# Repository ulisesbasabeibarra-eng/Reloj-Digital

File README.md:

# Reloj Digital

## Authors

- [@Ulises Basabe](https://github.com/ulisesbasabeibarra-eng)
- [@Facundo Dominguez](https://github.com/facundodominguez1)
- [@Ramiro Trejo](https://github.com/RamiiTrejo)
- [@Rodrigo Benitez](https://github.com/rodrigobenitez17)
- [@Maximo Paez]()

## DESCRIPCIÓN

Un reloj digital sin utilizar un microcontrolador o web para establecer el tiempo. Utilizando solamente electronica discreta como el lm555, cuyo componente debe de estar en modo astable para general pulsos electronicos que estableceran gracias a los integrados 74LS47 y 74LS90 que los displays de 7 segmentos marquen una hora determinada. Un total de 6 displays para marcar los segundos, minutos y horas.
## Informe

[Video en proteus](https://www.youtube.com/watch?v=-MJHPHdGoc4)

[Reloj Digital](https://docs.google.com/document/d/12YXhhFJf7GPLBze2eZ5sYaiuNMOwRFxj9prBwNTrKLU/edit?pli=1&tab=t.0#heading=h.a97jr9uy2bgi)
. Este enlace lleva a un documento de google en el que se encuentra más informacion sobre este projecto junto con imagenes explicativas y vistas previas.
## Funcionamiento
El funcionamiento de este reloj se basa en el circuito integrado LM555, configurado como oscilador astable, que genera una serie de pulsos eléctricos aproximadamente de 1 Hz por  segundo. Estos pulsos son enviados al 74LS90, que actúa como contador decimal y convierte los pulsos en una salida binaria. Después, esta señal binaria pasa al 74LS47, que la decodifica y la transforma en señales para encender los segmentos correspondientes del display de 7 segmentos, mostrando así los números de forma digital. 

El potenciómetro permite ajustar la frecuencia del LM555, aumentando o disminuyendo la velocidad con que se generan los pulsos que llegan al 74LS90 (Es decir, la velocidad con que se cambian los números en el display).

El LED conectado al circuito también parpadea al ritmo de los pulsos, sirviendo como indicador visual de la frecuencia del contador. En este caso, se ha optado por utilizar una resistencia fija de 3,9 kΩ, de modo que el temporizador genere un pulso cada segundo aproximadamente, obteniendo así una base de tiempo estable para el reloj.

Los botones conectados uno a los displays de los segundos y otro conectado a los minutos. Su funcion es que una vez al ser pulsados, este pulso contara tambien como si fuera un pulso del LM555, es decir, una vez que se pulsa el numero del display pasara al siguiente respectivamente, funcionando como un reloj manual y esta para setiar el reloj a la hora exacta al de la hora actual.

(La alimentacion vendria mediante un cable conectado a un transformador el cual iria conectado a un toma corriente)
## Modelo 3D
En este projecto se utilizo Autodesk, plataforma de software el cual estoy mas acostumbrado a utilizar ademas de ser muy utilizadas a la hora de hacer diseños 3D, gracias a que este ofrece una amplia gama de software como AutoCAD, Fusion 360, Inventor y 3ds Max, utilizados en sectores como la ingeniería, la arquitectura, el entretenimiento y el diseño de productos.

El modelo 3D esta compuesto por dos partes principales: El piso y El cuerpo. 

El piso o la inferior, es un rectangulo compuesto por cuatro agujeros, uno en cada esquina, por donde se ingresarian los tornillos los cuales unirian las dos piezas. Además de tener otros cuatro agujeros más con un desnivel para ubicar la placa y mantenerla en el lugar y dejando un muy pequeño espacio entre los dos para las patas o sobresalientes de los componentes de la misma.

El Cuepo tambien consta con los mismos huecos para tener mas rigidez en la uniones de estas tres partes (placa, piso, cuerpo).Tambien consta con un agujero en un costado para permitir la salida del cable de alimentación.

Además tiene 6 agujeros rectangulares para permitir la vista de los displays de 7 segmento, con una pequeña separacion entre cada uno y otra entre cada grupo de dos, para formar los segundos, minutos y horas, cuyos grupos abajo les sigue sus respectivo unidad marcada como un corte en el cuerpo. Tambien, más abajo tiene dos agueros donde irian ubicados los botones. Los displays y los botones deberan ir adheridos con silicona para que mantengan su lugar.

En la carpeta carcasa, se encontran los archivos de estas pieza 3D en diferentes tipos de archivos desde .stl, donde se podran mandar a imprimir directamente, .fusion, asta .step. 
## Desmontaje de la carcasa

 se observa como se vería el diseño de la plaqueta en 3D para poder dimensionar los componentes y facilitar la comprension de las conexiones

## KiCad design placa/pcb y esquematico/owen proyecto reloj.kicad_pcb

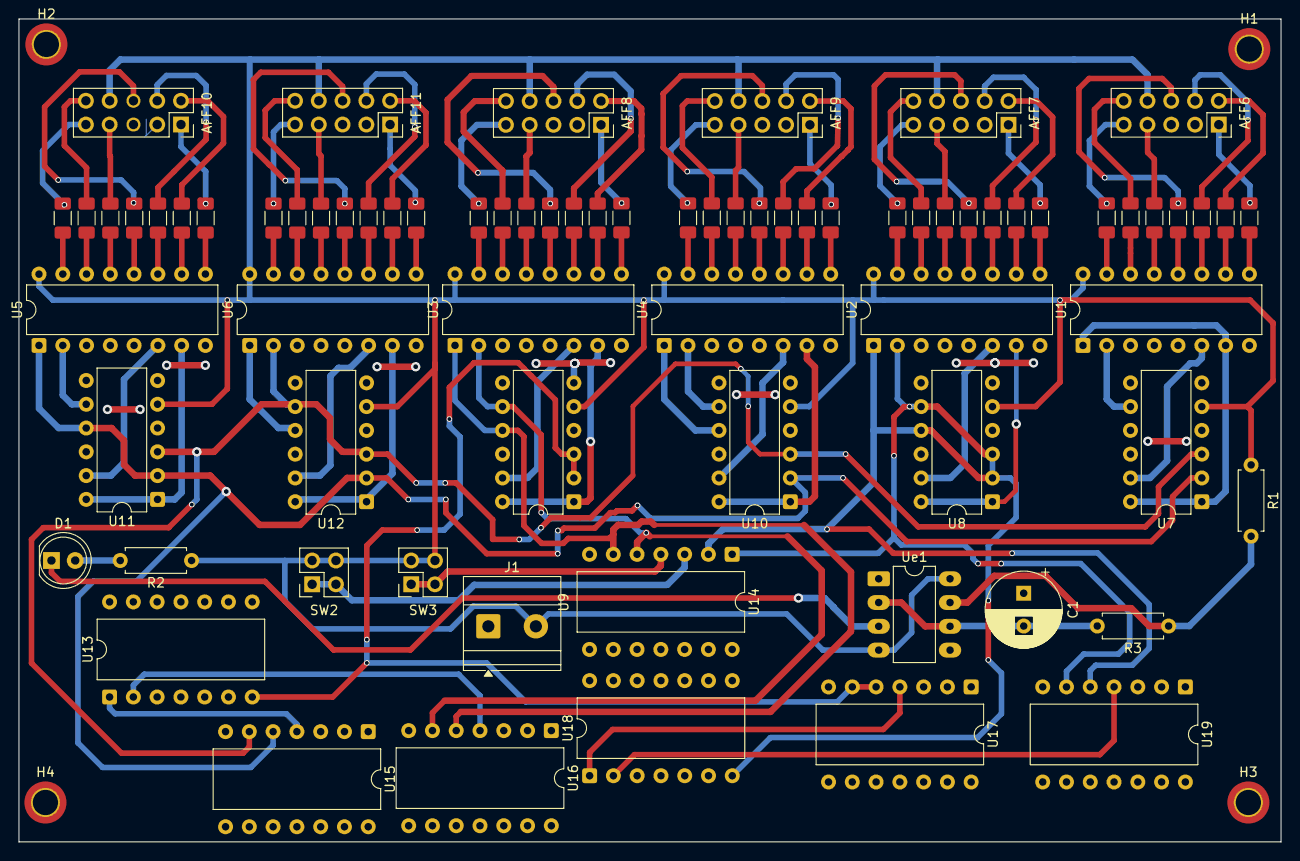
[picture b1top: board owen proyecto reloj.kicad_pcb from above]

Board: 2 copper layers, 134.8 x 87.9 mm, 80 parts (0 on the bottom side), 121 nets.

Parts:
AFF6, AFF7, AFF8, AFF9, AFF10, AFF11: LTS-6960HR; PinSocket_2x05_P2.54mm_Vertical
C1: C; CP_Radial_D8.0mm_P3.50mm
D1: LED; LED_D5.0mm
H1, H2, H3, H4: Mounting_Hole; MountingHole_2.7mm_M2.5_ISO14580_Pad_TopOnly
J1: Screw_Terminal_01x02; TerminalBlock_Phoenix_MKDS-1,5-2-5.08_1x02_P5.08mm_Horizont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
R1: 4.7K; R_Axial_DIN0207_L6.3mm_D2.5mm_P7.62mm_Horizontal
R2: 330; R_Axial_DIN0207_L6.3mm_D2.5mm_P7.62mm_Horizontal
R3: 3.9k; R_Axial_DIN0207_L6.3mm_D2.5mm_P7.62mm_Horizontal
R10, R11, R12, R13, R14, R15, R16, R17, R18, R19, R20, R21, R22, R23, R24, R25, R26, R27, R28, R29, R30, R31, R32, R33, R34, R35, R36, R37, R38, R39, R40, R41, R42, R43, R44, R45, R46, R47, R48, R49, R50, R51: 330; R_1206_3216Metric_Pad1.30x1.75mm_HandSolder
SW2, SW3: SW_MEC_5G; PinSocket_2x02_P2.54mm_Vertical
U1, U2, U3, U4, U5, U6: 74LS47; DIP-16_W7.62mm
U7, U8, U9, U10, U11, U12: 74LS90; DIP-12_W7.62mm
U13, U18: 74AUC2G32; DIP-14_W10.16mm
U14, U15, U16, U17, U19: 4081; DIP-14_W10.16mm
Ue1: LM555xM; DIP-8_W7.62mm_LongPads

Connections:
A1: AFF10.7 (a), R38.1
A2: AFF11.7 (a), R31.1
A3: AFF8.7 (a), R24.1
A4: AFF9.7 (a), R17.1
A5: AFF7.7 (a), R10.1
A6: AFF6.7 (a), R45.1
B1: AFF10.6 (b), R39.1
B2: AFF11.6 (b), R32.1
B3: AFF8.6 (b), R25.1
B4: AFF9.6 (b), R18.1
B5: AFF7.6 (b), R11.1
B6: AFF6.6 (b), R46.1
C1: AFF10.4 (c), R40.1
C2: AFF11.4 (c), R33.1
C3: AFF8.4 (c), R26.1
C4: AFF9.4 (c), R19.1
C5: AFF7.4 (c), R12.1
C6: AFF6.4 (c), R47.1
D1: AFF10.2 (d), R41.1
D2: AFF11.2 (d), R34.1
D3: AFF8.2 (d), R27.1
D4: AFF9.2 (d), R20.1
D5: AFF7.2 (d), R13.1
D6: AFF6.2 (d), R48.1
E1: AFF10.1 (e), R42.1
E2: AFF11.1 (e), R35.1
E3: AFF8.1 (e), R28.1
E4: AFF9.1 (e), R21.1
E5: AFF7.1 (e), R14.1
E6: AFF6.1 (e), R49.1
F1: AFF10.9 (f), R43.1
F2: AFF11.9 (f), R36.1
F3: AFF8.9 (f), R29.1
F4: AFF9.9 (f), R22.1
F5: AFF7.9 (f), R15.1
F6: AFF6.9 (f), R50.1
G1: AFF10.10 (g), R44.1
G2: AFF11.10 (g), R37.1
G3: AFF8.10 (g), R30.1
G4: AFF9.10 (g), R23.1
G5: AFF7.10 (g), R16.1
G6: AFF6.10 (g), R51.1
GND: C1.1, J1.1, U1.8 (GND), U2.8 (GND), U3.8 (GND), U4.8 (GND), U5.8 (GND), U6.8 (GND), U7.6 (R9(1)), U7.7 (R9(2)), U7.10 (GND), U8.6 (R9(1)), U8.7 (R9(2)), U8.10 (GND), U9.6 (R9(1)), U9.7 (R9(2)), U9.10 (GND), U10.6 (R9(1)), U10.7 (R9(2)), U10.10 (GND), U11.6 (R9(1)), U11.7 (R9(2)), U11.10 (GND), U12.6 (R9(1)), U12.7 (R9(2)), U12.10 (GND), Ue1.1 (GND)
unnamed: D1.2 (A), R2.2
unnamed: R45.2, U1.13 (a)
unnamed: R46.2, U1.12 (b)
unnamed: R47.2, U1.11 (c)
unnamed: R48.2, U1.10 (d)
unnamed: R49.2, U1.9 (e)
unnamed: R50.2, U1.15 (f)
unnamed: R51.2, U1.14 (g)
unnamed: R10.2, U2.13 (a)
unnamed: R11.2, U2.12 (b)
unnamed: R12.2, U2.11 (c)
unnamed: R13.2, U2.10 (d)
unnamed: R14.2, U2.9 (e)
unnamed: R15.2, U2.15 (f)
unnamed: R16.2, U2.14 (g)
unnamed: R24.2, U3.13 (a)
unnamed: R25.2, U3.12 (b)
unnamed: R26.2, U3.11 (c)
unnamed: R27.2, U3.10 (d)
unnamed: R28.2, U3.9 (e)
unnamed: R29.2, U3.15 (f)
unnamed: R30.2, U3.14 (g)
unnamed: R17.2, U4.13 (a)
unnamed: R18.2, U4.12 (b)
unnamed: R19.2, U4.11 (c)
unnamed: R20.2, U4.10 (d)
unnamed: R21.2, U4.9 (e)
unnamed: R22.2, U4.15 (f)
unnamed: R23.2, U4.14 (g)
unnamed: R38.2, U5.13 (a)
unnamed: R39.2, U5.12 (b)
unnamed: R40.2, U5.11 (c)
unnamed: R41.2, U5.10 (d)
unnamed: R42.2, U5.9 (e)
unnamed: R43.2, U5.15 (f)
unnamed: R44.2, U5.14 (g)
unnamed: R31.2, U6.13 (a)
unnamed: R32.2, U6.12 (b)
unnamed: R33.2, U6.11 (c)
unnamed: R34.2, U6.10 (d)
unnamed: R35.2, U6.9 (e)
unnamed: R36.2, U6.15 (f)
unnamed: R37.2, U6.14 (g)
unnamed: U13.1, U15.4
unnamed: U13.2, U16.4
unnamed: U17.4, U18.1
unnamed: U18.2, U19.4
unnamed: R1.2, R3.1, Ue1.7 (DIS)
Out: D1.1 (K), Ue1.3 (Q)
Q0: U5.7 (A), U11.1 (CP1..3), U11.12 (Q0)
Q1: U5.1 (B), U7.2 (R0(1)), U10.2 (R0(1)), U11.2 (R0(1)), U11.9 (Q1), U12.2 (R0(1)), U15.5
Q3: U5.2 (C), U11.8 (Q2)
Q4: U5.6 (D), U11.11 (Q3)
Q5: U6.7 (A), U12.1 (CP1..3), U12.12 (Q0)
Q6: U6.1 (B), U12.9 (Q1)
Q7: U6.2 (C), U7.3 (R0(2)), U10.3 (R0(2)), U11.3 (R0(2)), U12.3 (R0(2)), U12.8 (Q2), U15.6
Q8: U6.6 (D), U12.11 (Q3)
Q9: U3.7 (A), U9.1 (CP1..3), U9.12 (Q0)
Q10: U3.1 (B), U9.9 (Q1), U14.6, U16.5
Q11: U3.2 (C), U9.8 (Q2), U14.5, U16.6
Q12: U3.6 (D), U9.11 (Q3)
Q13: U4.7 (A), U10.1 (CP1..3), U10.12 (Q0)
Q14: U4.1 (B), U10.9 (Q1)
Q15: U4.2 (C), U10.8 (Q2)
Q16: U4.6 (D), U10.11 (Q3)
Q17: U2.7 (A), U8.1 (CP1..3), U8.12 (Q0)
Q18: U2.1 (B), U8.9 (Q1), U14.2, U19.5
Q19: U2.2 (C), U8.8 (Q2), U14.1, U19.6
Q20: U2.6 (D), U8.11 (Q3)
Q21: U1.1 (B), U1.7 (A), U7.1 (CP1..3), U7.12 (Q0)
Q23: U1.2 (C), U7.8 (Q2)
Q24: U1.6 (D), U7.11 (Q3)
R1: U9.2 (R0(1)), U9.3 (R0(2)), U13.7, U17.5, U17.6
R2: U8.2 (R0(1)), U8.3 (R0(2)), U18.7
Trig: C1.2, R3.2, Ue1.2 (TR), Ue1.6 (THR)
VCC: AFF6.3 (C.A.), AFF6.8 (C.A.), AFF7.3 (C.A.), AFF7.8 (C.A.), AFF8.3 (C.A.), AFF8.8 (C.A.), AFF9.3 (C.A.), AFF9.8 (C.A.), AFF10.8 (C.A.), AFF11.3 (C.A.), AFF11.8 (C.A.), J1.2, R1.1, R2.1, SW2.3 (B), SW2.4 (B), SW3.3 (B), SW3.4 (B), U1.16 (VCC), U2.16 (VCC), U3.16 (VCC), U4.16 (VCC), U5.16 (VCC), U6.16 (VCC), U7.5 (VCC), U8.5 (VCC), U9.5 (VCC), U10.5 (VCC), U11.5 (VCC), U12.5 (VCC), Ue1.4 (R), Ue1.8 (VCC)
cp0: SW3.1 (A), SW3.2 (A), U14.4
cp1: SW2.1 (A), SW2.2 (A), U14.3

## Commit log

2025-10-10 Create asd
2025-10-10 Create as
2025-10-10 Create arw
2025-10-10 Create asdf
2025-10-12 Create Proteus
2025-10-12 Create d
2025-10-16 Create Video simulación en proteus
2025-10-16 Rename simulación.pdsprj to archivo en proteus. simulación.pdsprj
2025-10-17 Create aaaaaa
2025-10-17 Create Informe world
2025-10-18 Create video partes
2025-10-23 owen proyecto. rar
2025-10-23 Rename README.md to README.md
2025-10-23 Fix header formatting in README.md
2025-10-23 Update Informe world
2025-10-23 Update link in Informe world
2025-10-23 Remove 'd' from Informe world file
2025-10-23 Update link with additional heading reference
2025-10-23 Fix hyperlink syntax in Informe world
2025-10-24 Revise README with project details and authors
    Updated README to include authors, project description, and an image link.
2025-10-24 Update Video simulación en proteus
2025-10-24 README
    Corrected typos and improved clarity in the README.
2025-10-24 README.md
2025-10-24 Update README.md
    Updated the project description for clarity and detail.
2025-10-24 Create aad
2025-10-24 Create Objetos 3d
2025-10-24 Add new file 'asd' in 'Objetos 3d' directory
2025-10-24 Create a
2025-10-25 Mejora README.md
    Se realizaron correcciones gramaticales
2025-10-25 in README
2025-10-25 README.md
    README.
2025-10-25 ESQUEMATICO Y PCB README
2025-10-25 pcb y esq
2025-10-25 Fix typos in README.md
2025-11-02 README
    Removed detailed section about schematic and PCB design using KICAD, including images and explanations.
2025-11-06 Update video link for simulation in Proteus video
2025-11-06 Update README with video and document links
    Added a link to a video demonstration and a Google document for more information about the digital clock project.
2025-11-07 Create INFORME RELOJ DIGITAL
